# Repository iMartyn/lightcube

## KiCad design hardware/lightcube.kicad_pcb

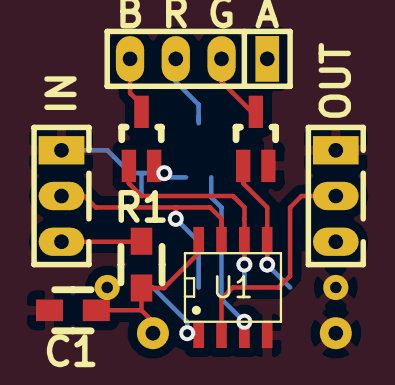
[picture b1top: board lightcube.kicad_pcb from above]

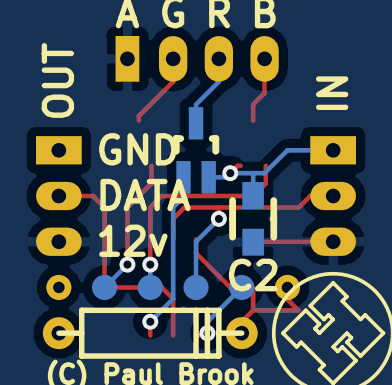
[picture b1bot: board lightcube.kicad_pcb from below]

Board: 2 copper layers, 13 parts (5 on the bottom side), 12 nets.

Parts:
C1: 100n; Capacitor_SMD0805_HandSoldering_RevA_Date21Jun2010
C2: 10u; Capacitor_SMD0805_HandSoldering_RevA_Date21Jun2010
D1: 5v1; D4
LOGO_SMALL: VAL**; LOGO_SMALL
P1: IN; JST-3
P2: OUT; JST-3
P3: LED; SIL-4-ELL
P4: PROG; prog_pads
Q1, Q2, Q3: MOSFET_N; SOT23_Transistor_Handsoldering_GDS
R1: 4k7; Resistor_SMD0805_HandSoldering_RevA_Date21Jun2010
U1: ATTINY25-SS; SO8E

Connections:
/5v: C1.1, D1.2, P4.1, R1.2, U1.8
/12v: C2.1, P1.3, P2.3, P3.1, R1.1
/B: P4.4, Q3.G, U1.6
/Bl: P3.4, Q3.D
/DI: P1.2, P4.3, U1.7
/DO: P2.2, U1.2
/G: P4.5, Q1.G, U1.5
/GND: C1.2, C2.2, D1.1, P1.1, P2.1, P4.6, Q1.S, Q2.S, Q3.S, U1.4
/Gl: P3.2, Q1.D
/R: Q2.G, U1.3
/RESET: P4.2, U1.1
/Rl: P3.3, Q2.D

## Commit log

2014-08-12 Initial hardware design
2014-08-12 Initial firmware commit
2014-08-12 Add programming pads
2014-08-14 Silkscreen tweak
2014-09-12 Add test sketches
